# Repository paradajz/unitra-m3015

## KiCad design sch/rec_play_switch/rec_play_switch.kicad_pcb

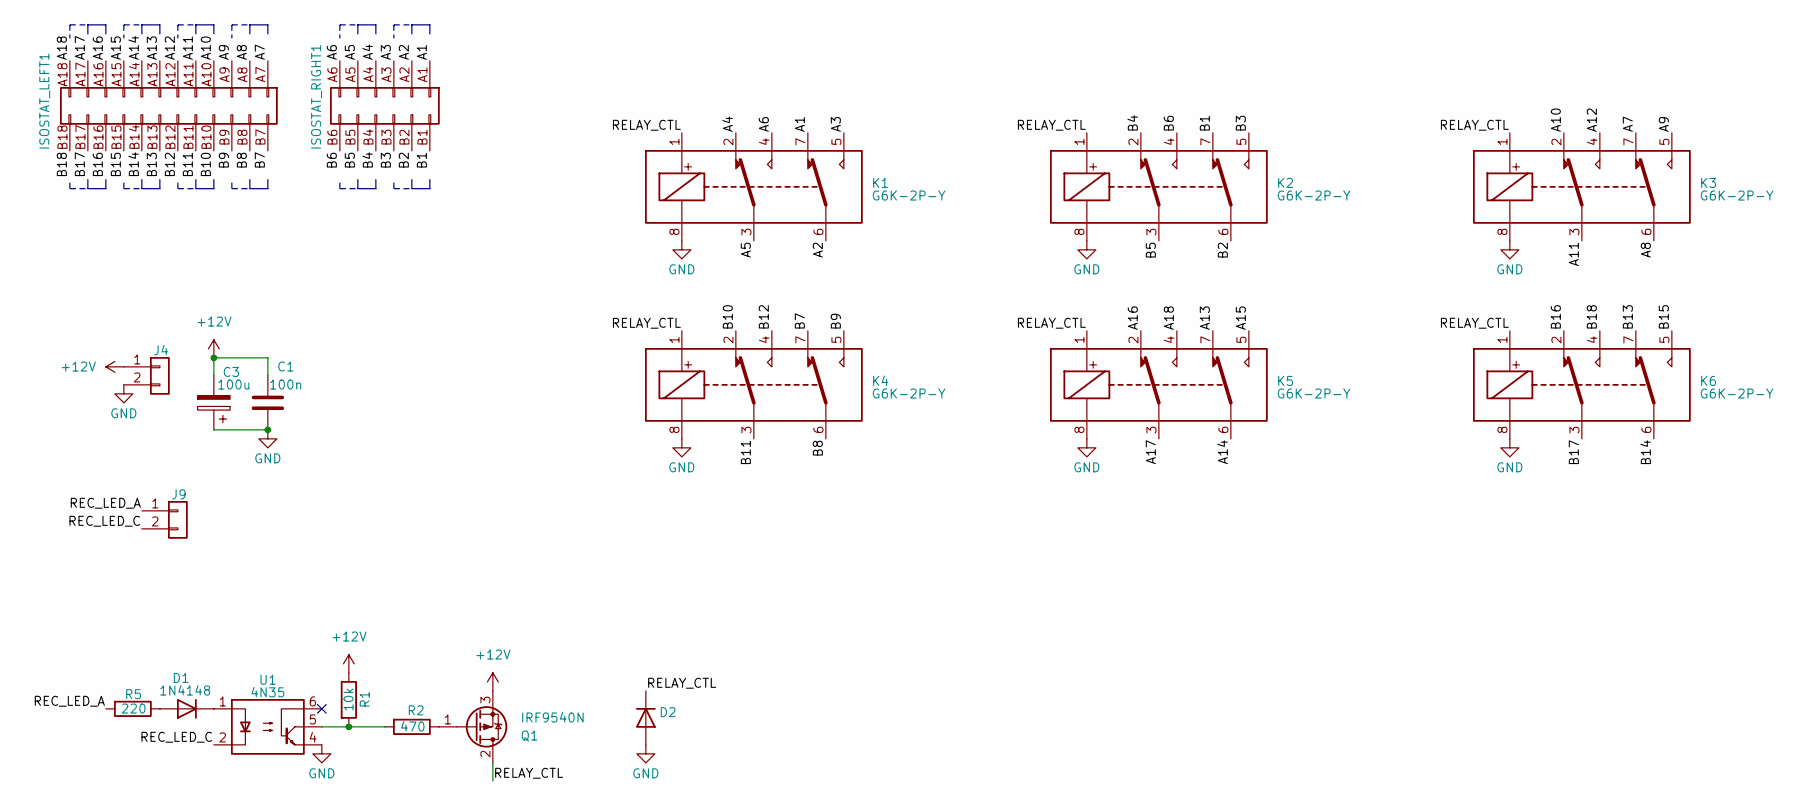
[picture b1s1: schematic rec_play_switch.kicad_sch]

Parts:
C1: 100n; C_Disc_D5.0mm_W2.5mm_P5.00mm; LCSC C1525
C3: 100u; CP_Radial_D5.0mm_P2.50mm; LCSC C116241
D1: 1N4148; D_DO-35_SOD27_P7.62mm_Horizontal
D2: 1N4007; D_DO-35_SOD27_P7.62mm_Horizontal
ISOSTAT_LEFT1: Conn_02x12_Row_Letter_Last; PinHeader_2x12_P2.54mm_Vertical
ISOSTAT_RIGHT1: Conn_02x06_Row_Letter_Last; PinHeader_2x06_P2.54mm_Vertical
J4, J9: Conn_01x02; JST_XH_B2B-XH-A_1x02_P2.50mm_Vertical; LCSC C158012
K1, K2, K3, K4, K5, K6: G6K-2P-Y; Relay_DPDT_Omron_G6K-2P
Q1: IRF9540N; TO-220-3_Vertical
R1: 10k; R_Axial_DIN0207_L6.3mm_D2.5mm_P10.16mm_Horizontal
R2: 470; R_Axial_DIN0207_L6.3mm_D2.5mm_P10.16mm_Horizontal
R5: 220; R_Axial_DIN0207_L6.3mm_D2.5mm_P10.16mm_Horizontal
U1: 4N35; DIP-6_W7.62mm; LCSC C57084

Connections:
+12V: C1.2, C3.2, J4.1, Q1.3 (S), R1.1
/A1: ISOSTAT_RIGHT1.A1, K1.7
/A2: ISOSTAT_RIGHT1.A2, K1.6
/A3: ISOSTAT_RIGHT1.A3, K1.5
/A4: ISOSTAT_RIGHT1.A4, K1.2
/A5: ISOSTAT_RIGHT1.A5, K1.3
/A6: ISOSTAT_RIGHT1.A6, K1.4
/A7: ISOSTAT_LEFT1.A7, K3.7
/A8: ISOSTAT_LEFT1.A8, K3.6
/A9: ISOSTAT_LEFT1.A9, K3.5
/A10: ISOSTAT_LEFT1.A10, K3.2
/A11: ISOSTAT_LEFT1.A11, K3.3
/A12: ISOSTAT_LEFT1.A12, K3.4
/A13: ISOSTAT_LEFT1.A13, K5.7
/A14: ISOSTAT_LEFT1.A14, K5.6
/A15: ISOSTAT_LEFT1.A15, K5.5
/A16: ISOSTAT_LEFT1.A16, K5.2
/A17: ISOSTAT_LEFT1.A17, K5.3
/A18: ISOSTAT_LEFT1.A18, K5.4
/B1: ISOSTAT_RIGHT1.B1, K2.7
/B2: ISOSTAT_RIGHT1.B2, K2.6
/B3: ISOSTAT_RIGHT1.B3, K2.5
/B4: ISOSTAT_RIGHT1.B4, K2.2
/B5: ISOSTAT_RIGHT1.B5, K2.3
/B6: ISOSTAT_RIGHT1.B6, K2.4
/B7: ISOSTAT_LEFT1.B7, K4.7
/B8: ISOSTAT_LEFT1.B8, K4.6
/B9: ISOSTAT_LEFT1.B9, K4.5
/B10: ISOSTAT_LEFT1.B10, K4.2
/B11: ISOSTAT_LEFT1.B11, K4.3
/B12: ISOSTAT_LEFT1.B12, K4.4
/B13: ISOSTAT_LEFT1.B13, K6.7
/B14: ISOSTAT_LEFT1.B14, K6.6
/B15: ISOSTAT_LEFT1.B15, K6.5
/B16: ISOSTAT_LEFT1.B16, K6.2
/B17: ISOSTAT_LEFT1.B17, K6.3
/B18: ISOSTAT_LEFT1.B18, K6.4
/REC_LED_A: J9.1, R5.2
/REC_LED_C: J9.2, U1.2
/RELAY_CTL: D2.1 (K), K1.1, K2.1, K3.1, K4.1, K5.1, K6.1, Q1.2 (D)
GND: C1.1, C3.1, D2.2 (A), J4.2, K1.8, K2.8, K3.8, K4.8, K5.8, K6.8, U1.4
unnamed: D1.2 (A), R5.1
unnamed: D1.1 (K), U1.1
unnamed: Q1.1 (G), R2.1
unnamed: R1.2, R2.2, U1.5

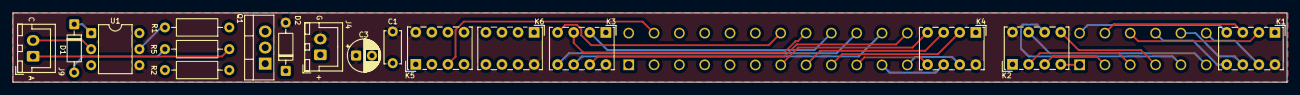
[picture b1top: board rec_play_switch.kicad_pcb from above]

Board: 4 copper layers, 201.2 x 10.9 mm, 19 parts (0 on the bottom side), 45 nets.

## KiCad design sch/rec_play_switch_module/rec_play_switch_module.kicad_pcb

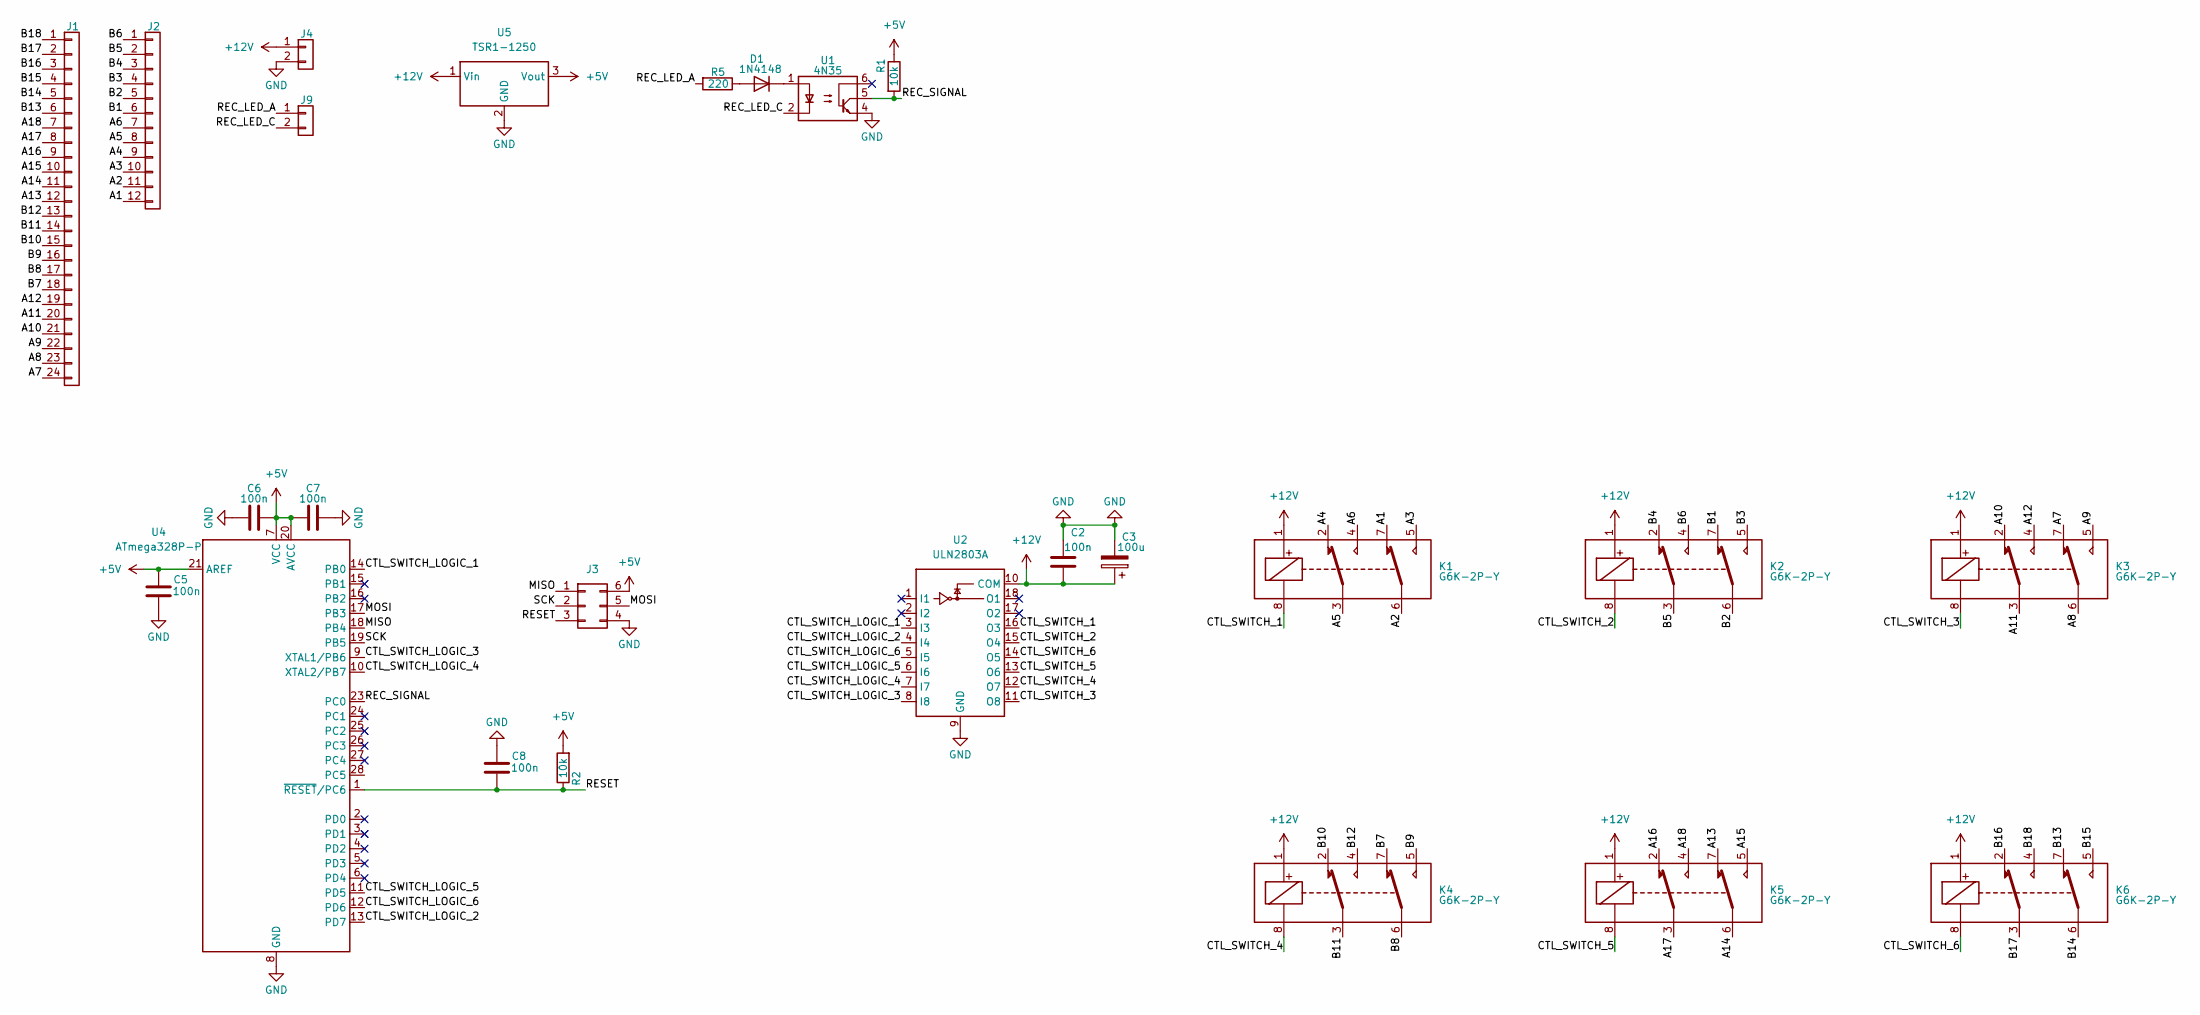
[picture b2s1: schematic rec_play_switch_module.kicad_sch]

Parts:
C2, C5, C6, C7, C8: 100n; C_Disc_D5.0mm_W2.5mm_P5.00mm; LCSC C1525
C3: 100u; CP_Radial_D5.0mm_P2.50mm; LCSC C116241
D1: 1N4148; D_DO-35_SOD27_P7.62mm_Horizontal
J1: Conn_01x24; PinHeader_1x24_P1.27mm_Vertical
J2: Conn_01x12; PinHeader_1x12_P1.27mm_Vertical
J3: Conn_02x03_Counter_Clockwise; PinHeader_2x03_P2.54mm_Vertical
J4, J9: Conn_01x02; JST_XH_B2B-XH-A_1x02_P2.50mm_Vertical; LCSC C158012
K1, K2, K3, K4, K5, K6: G6K-2P-Y; Relay_DPDT_Omron_G6K-2P
R1, R2: 10k; R_Axial_DIN0207_L6.3mm_D2.5mm_P10.16mm_Horizontal
R5: 220; R_Axial_DIN0207_L6.3mm_D2.5mm_P10.16mm_Horizontal
U1: 4N35; DIP-6_W7.62mm; LCSC C57084
U2: ULN2803A; DIP-18_W7.62mm
U4: ATmega328P-P; DIP-28_W7.62mm
U5: TSR1-1250; Converter_DCDC_TRACO_TSR1-xxxxE_THT; LCSC C6886877

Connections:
+5V: C5.1, C6.2, C7.1, J3.6, R1.1, R2.2, U4.7 (VCC), U4.20 (AVCC), U4.21 (AREF), U5.3 (Vout)
+12V: C2.1, C3.1, J4.1, K1.1, K2.1, K3.1, K4.1, K5.1, K6.1, U2.10 (COM), U5.1 (Vin)
/A1: J2.12, K1.7
/A2: J2.11, K1.6
/A3: J2.10, K1.5
/A4: J2.9, K1.2
/A5: J2.8, K1.3
/A6: J2.7, K1.4
/A7: J1.24, K3.7
/A8: J1.23, K3.6
/A9: J1.22, K3.5
/A10: J1.21, K3.2
/A11: J1.20, K3.3
/A12: J1.19, K3.4
/A13: J1.12, K5.7
/A14: J1.11, K5.6
/A15: J1.10, K5.5
/A16: J1.9, K5.2
/A17: J1.8, K5.3
/A18: J1.7, K5.4
/B1: J2.6, K2.7
/B2: J2.5, K2.6
/B3: J2.4, K2.5
/B4: J2.3, K2.2
/B5: J2.2, K2.3
/B6: J2.1, K2.4
/B7: J1.18, K4.7
/B8: J1.17, K4.6
/B9: J1.16, K4.5
/B10: J1.15, K4.2
/B11: J1.14, K4.3
/B12: J1.13, K4.4
/B13: J1.6, K6.7
/B14: J1.5, K6.6
/B15: J1.4, K6.5
/B16: J1.3, K6.2
/B17: J1.2, K6.3
/B18: J1.1, K6.4
/CTL_SWITCH_1: K1.8, U2.16 (O3)
/CTL_SWITCH_2: K2.8, U2.15 (O4)
/CTL_SWITCH_3: K3.8, U2.11 (O8)
/CTL_SWITCH_4: K4.8, U2.12 (O7)
/CTL_SWITCH_5: K5.8, U2.13 (O6)
/CTL_SWITCH_6: K6.8, U2.14 (O5)
/CTL_SWITCH_LOGIC_1: U2.3 (I3), U4.14 (PB0)
/CTL_SWITCH_LOGIC_2: U2.4 (I4), U4.13 (PD7)
/CTL_SWITCH_LOGIC_3: U2.8 (I8), U4.9 (XTAL1/PB6)
/CTL_SWITCH_LOGIC_4: U2.7 (I7), U4.10 (XTAL2/PB7)
/CTL_SWITCH_LOGIC_5: U2.6 (I6), U4.11 (PD5)
/CTL_SWITCH_LOGIC_6: U2.5 (I5), U4.12 (PD6)
/MISO: J3.1, U4.18 (PB4)
/MOSI: J3.5, U4.17 (PB3)
/REC_LED_A: J9.1, R5.2
/REC_LED_C: J9.2, U1.2
/REC_SIGNAL: R1.2, U1.5, U4.23 (PC0)
/RESET: C8.2, J3.3, R2.1, U4.1 (~RESET/PC6)
/SCK: J3.2, U4.19 (PB5)
GND: C2.2, C3.2, C5.2, C6.1, C7.2, C8.1, J3.4, J4.2, U1.4, U2.9 (GND), U4.8 (GND), U4.22 (GND), U5.2 (GND)
unnamed: D1.2 (A), R5.1
unnamed: D1.1 (K), U1.1

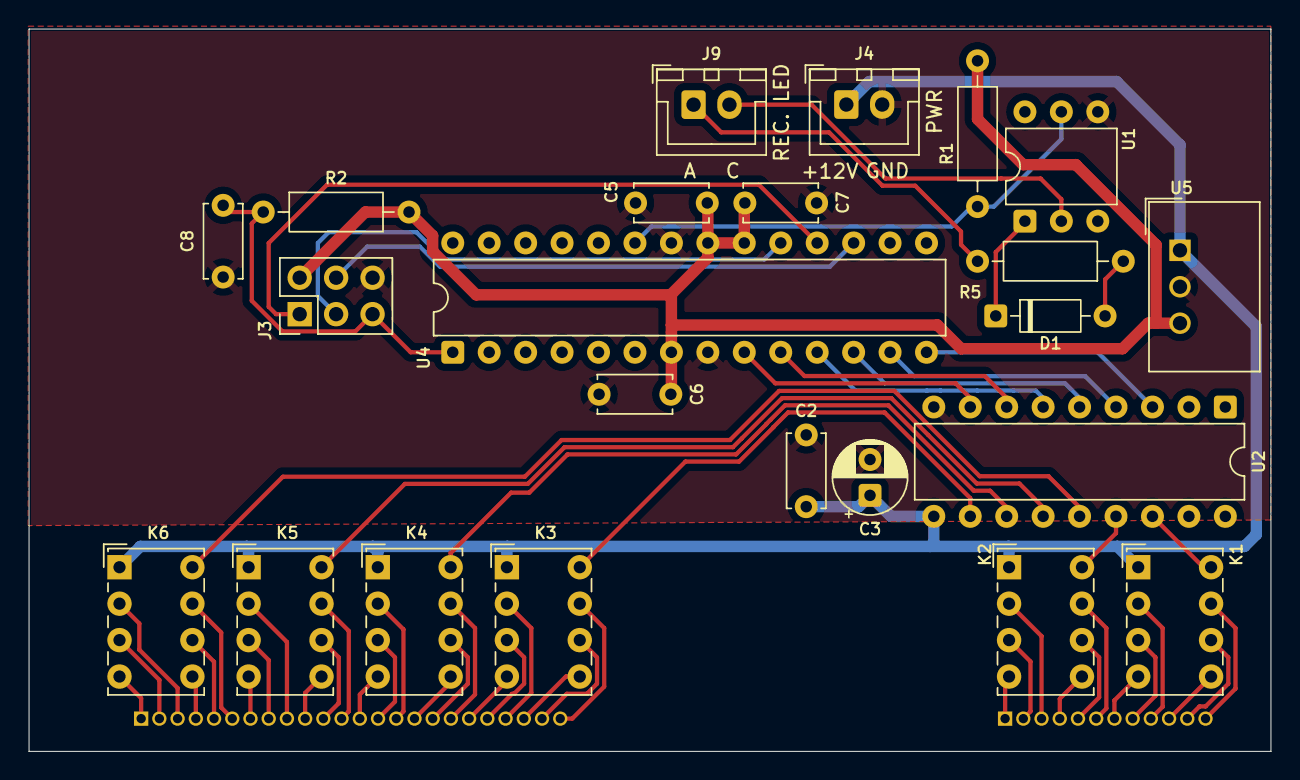
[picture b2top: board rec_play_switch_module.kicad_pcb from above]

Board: 2 copper layers, 86.6 x 50.3 mm, 25 parts (0 on the bottom side), 60 nets.

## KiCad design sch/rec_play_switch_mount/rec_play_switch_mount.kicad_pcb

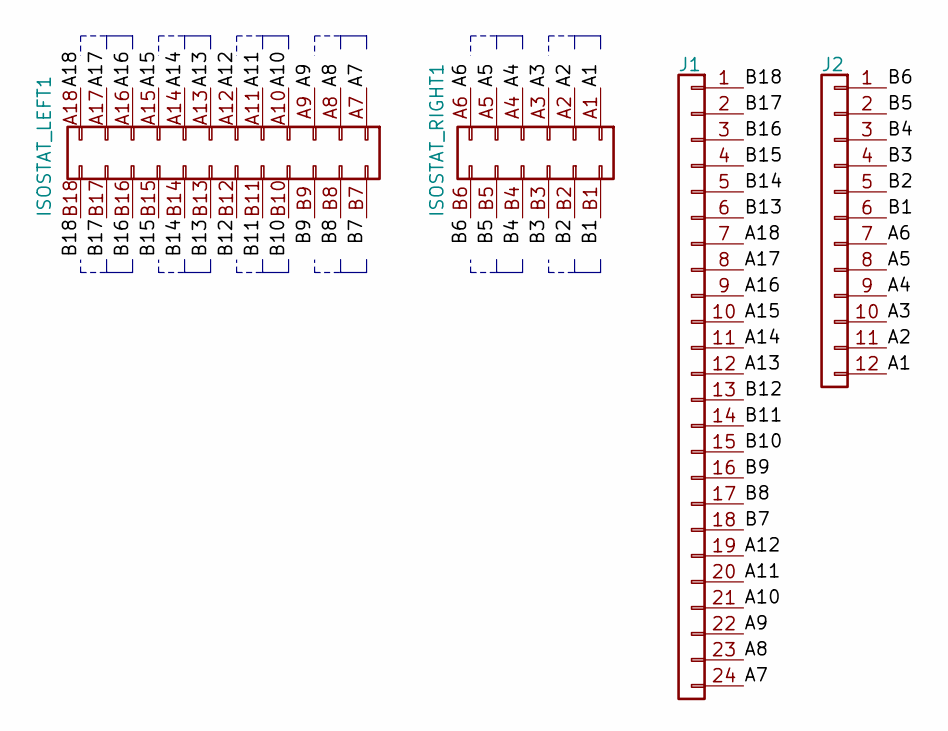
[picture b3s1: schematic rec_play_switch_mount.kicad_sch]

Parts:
ISOSTAT_LEFT1: Conn_02x12_Row_Letter_Last; PinHeader_2x12_P2.54mm_Vertical
ISOSTAT_RIGHT1: Conn_02x06_Row_Letter_Last; PinHeader_2x06_P2.54mm_Vertical
J1: Conn_01x24; PinHeader_1x24_P1.27mm_Vertical
J2: Conn_01x12; PinHeader_1x12_P1.27mm_Vertical

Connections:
/A1: ISOSTAT_RIGHT1.A1, J2.12
/A2: ISOSTAT_RIGHT1.A2, J2.11
/A3: ISOSTAT_RIGHT1.A3, J2.10
/A4: ISOSTAT_RIGHT1.A4, J2.9
/A5: ISOSTAT_RIGHT1.A5, J2.8
/A6: ISOSTAT_RIGHT1.A6, J2.7
/A7: ISOSTAT_LEFT1.A7, J1.24
/A8: ISOSTAT_LEFT1.A8, J1.23
/A9: ISOSTAT_LEFT1.A9, J1.22
/A10: ISOSTAT_LEFT1.A10, J1.21
/A11: ISOSTAT_LEFT1.A11, J1.20
/A12: ISOSTAT_LEFT1.A12, J1.19
/A13: ISOSTAT_LEFT1.A13, J1.12
/A14: ISOSTAT_LEFT1.A14, J1.11
/A15: ISOSTAT_LEFT1.A15, J1.10
/A16: ISOSTAT_LEFT1.A16, J1.9
/A17: ISOSTAT_LEFT1.A17, J1.8
/A18: ISOSTAT_LEFT1.A18, J1.7
/B1: ISOSTAT_RIGHT1.B1, J2.6
/B2: ISOSTAT_RIGHT1.B2, J2.5
/B3: ISOSTAT_RIGHT1.B3, J2.4
/B4: ISOSTAT_RIGHT1.B4, J2.3
/B5: ISOSTAT_RIGHT1.B5, J2.2
/B6: ISOSTAT_RIGHT1.B6, J2.1
/B7: ISOSTAT_LEFT1.B7, J1.18
/B8: ISOSTAT_LEFT1.B8, J1.17
/B9: ISOSTAT_LEFT1.B9, J1.16
/B10: ISOSTAT_LEFT1.B10, J1.15
/B11: ISOSTAT_LEFT1.B11, J1.14
/B12: ISOSTAT_LEFT1.B12, J1.13
/B13: ISOSTAT_LEFT1.B13, J1.6
/B14: ISOSTAT_LEFT1.B14, J1.5
/B15: ISOSTAT_LEFT1.B15, J1.4
/B16: ISOSTAT_LEFT1.B16, J1.3
/B17: ISOSTAT_LEFT1.B17, J1.2
/B18: ISOSTAT_LEFT1.B18, J1.1

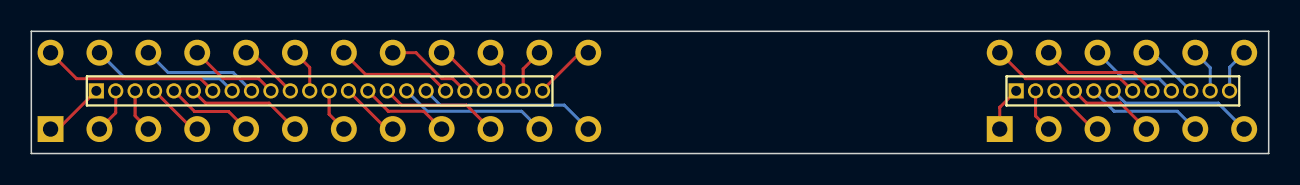
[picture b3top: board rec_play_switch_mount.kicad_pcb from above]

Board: 2 copper layers, 81.0 x 8.0 mm, 4 parts (0 on the bottom side), 36 nets.
